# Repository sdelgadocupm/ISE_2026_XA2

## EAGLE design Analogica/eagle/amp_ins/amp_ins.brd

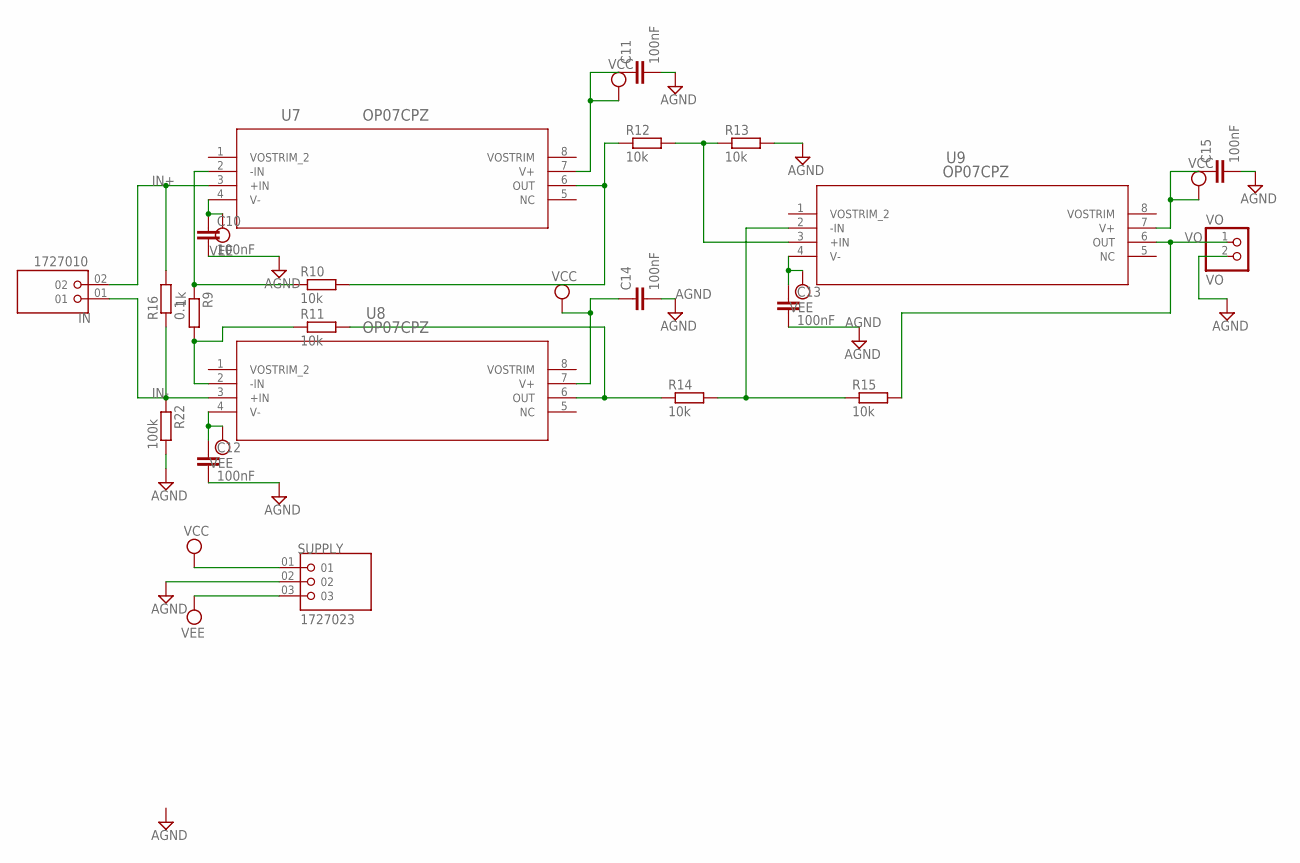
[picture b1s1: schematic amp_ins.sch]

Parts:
C10, C11, C12, C13, C14, C15: 100nF; C075-042X103
IN: 1727010; PHOENIX_1727010
R9: 1k; 0207/10
R10, R11, R12, R13, R14, R15: 10k; 0207/10
R16: 0.1; 0617/17
R22: 100k; 0207/10
SUPPLY: 1727023; PHOENIX_1727023
U7, U8, U9: OP07CPZ; N_8_ADI
VO: VO; 1X02

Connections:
AGND: C10.2, C11.2, C12.2, C13.2, C14.2, C15.2, R13.2, R22.2, SUPPLY.02, VO.2
IN+: IN.02, R16.2, U7.3 (+IN)
IN-: IN.01, R16.1, R22.1, U8.3 (+IN)
unnamed: R9.1, R10.1, U7.2 (-IN)
unnamed: R9.2, R11.1, U8.2 (-IN)
unnamed: R11.2, R14.1, U8.6 (OUT)
unnamed: R10.2, R12.1, U7.6 (OUT)
unnamed: R12.2, R13.1, U9.3 (+IN)
unnamed: R14.2, R15.1, U9.2 (-IN)
VCC: C11.1, C14.1, C15.1, SUPPLY.01, U7.7 (V+), U8.7 (V+), U9.7 (V+)
VEE: C10.1, C12.1, C13.1, SUPPLY.03, U7.4 (V-), U8.4 (V-), U9.4 (V-)
VO: R15.2, U9.6 (OUT), VO.1

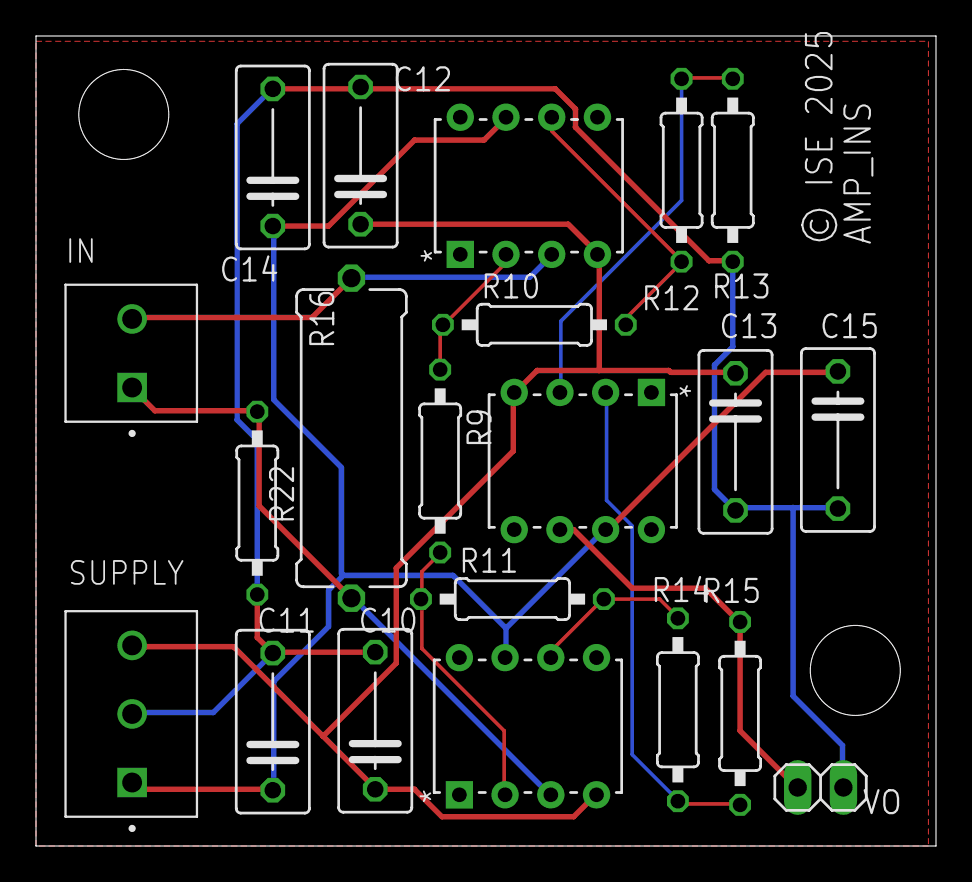
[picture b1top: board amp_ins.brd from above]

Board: 2 copper layers, 50.0 x 45.0 mm, 21 parts (0 on the bottom side), 12 nets.

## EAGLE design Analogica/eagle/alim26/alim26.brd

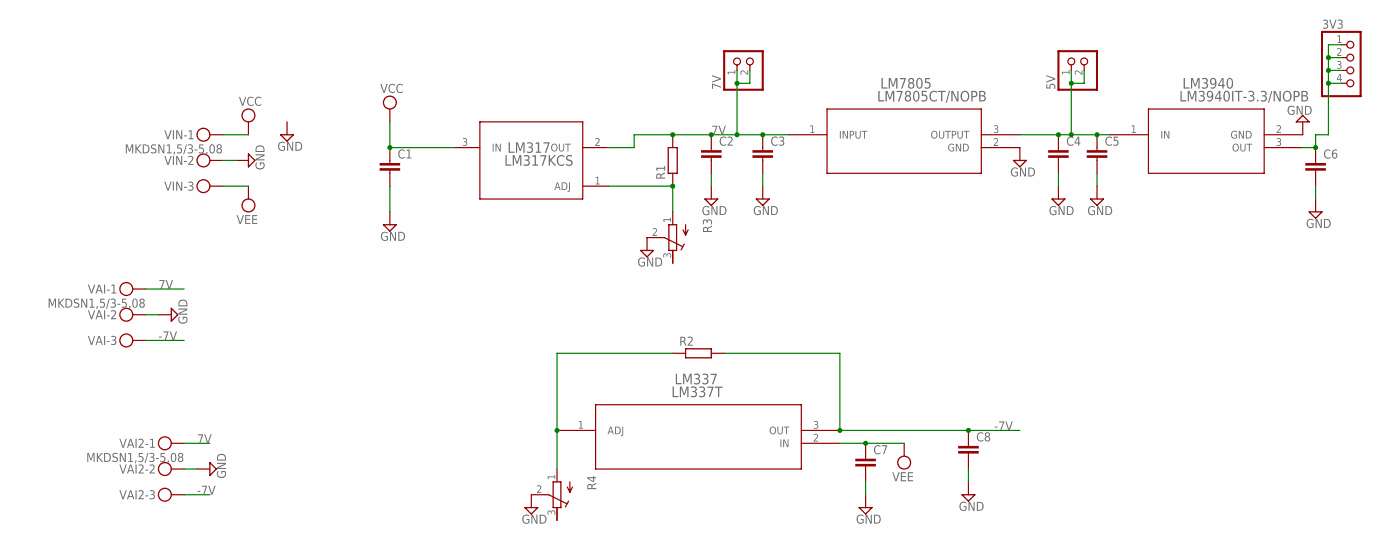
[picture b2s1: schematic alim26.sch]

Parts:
3V3: PINHD-1X4; 1X04
5V, 7V: PINHD-1X2; 1X02
C1, C2, C3, C4, C5, C6, C7, C8: C5/3; C5B3
LM317: LM317KCS; KCS0003A
LM337: LM337T; T03B_TEX
LM3940: LM3940IT-3.3/NOPB; T03B
LM7805: LM7805CT/NOPB; NDE3_TEX
R1, R2: R-EU_0207/10; 0207/10
R3, R4: R-TRIMM64Y; RTRIM64Y
VAI, VAI2: MKDSN1,5/3-5,08
VIN: MKDSN1,5/3-5,08

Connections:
7V: 7V.1, 7V.2, C2.1, C3.1, LM317.2 (OUT), LM7805.1 (INPUT), R1.2, VAI.1, VAI2.1
-7V: C8.1, LM337.3 (OUT), R2.2, VAI.3, VAI2.3
GND: C1.2, C2.2, C3.2, C4.2, C5.2, C6.2, C7.2, C8.2, LM3940.2 (GND), LM7805.2 (GND), R3.2 (S), R4.2 (S), VAI.2, VAI2.2, VIN.2
unnamed: LM317.1 (ADJ), R1.1, R3.1 (A)
unnamed: 5V.1, 5V.2, C4.1, C5.1, LM3940.1 (IN), LM7805.3 (OUTPUT)
unnamed: 3V3.1, 3V3.2, 3V3.3, 3V3.4, C6.1, LM3940.3 (OUT)
unnamed: LM337.1 (ADJ), R2.1, R4.1 (A)
VCC: C1.1, LM317.3 (IN), VIN.1
VEE: C7.1, LM337.2 (IN), VIN.3

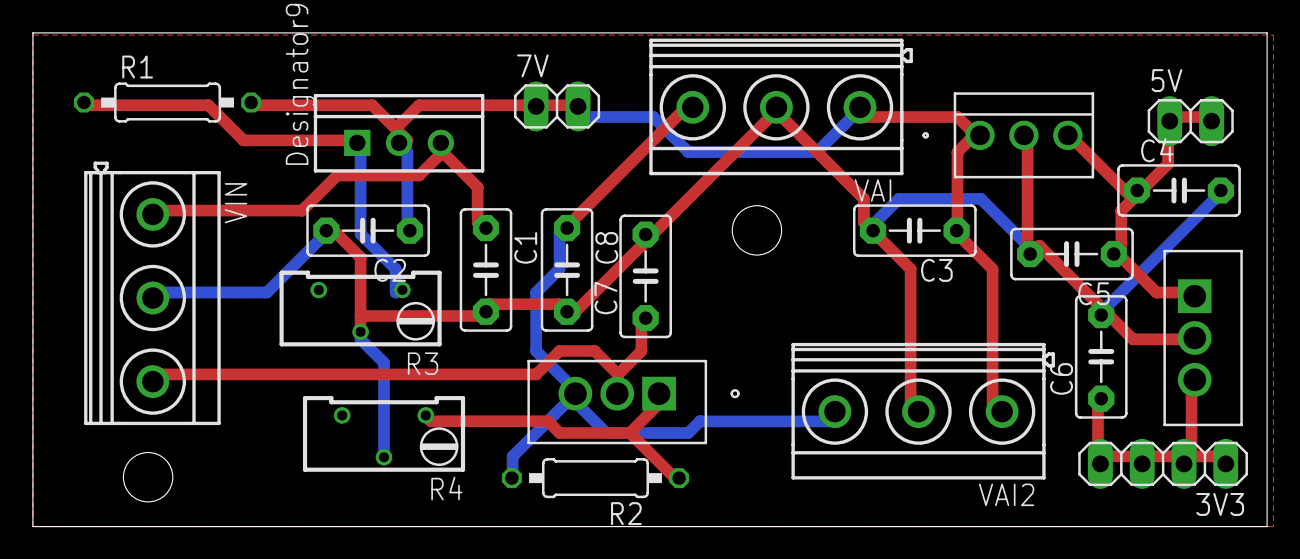
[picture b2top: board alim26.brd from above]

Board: 2 copper layers, 75.0 x 30.0 mm, 22 parts (0 on the bottom side), 9 nets.

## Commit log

2026-04-18 Placa Autonoma casi completa
2026-04-22 ajustes placa autónoma e idea de UART
2026-04-24 Placa autónoma funcionando completamente comentada
2026-04-24 Interfaz Web
2026-04-27 Primer commit de la placa master,USART y demas
2026-04-28 alimentacion y A.instrumentacion
2026-04-28 UART TX y RX
2026-04-29 Conexión entre placas comprobada
2026-04-29 Se me habia olvidado subir la slave
2026-04-30 UART para probar
2026-05-02 Comunicaciones terminadas junto con logger memoria
2026-05-02 cgi completo
2026-05-02 Master.c completo
2026-05-03 Codigo terminado, versiones casi finales de Autonoma y Master
2026-05-04 Filtro adc
2026-05-09 Perfeccionamiento Servidor + comentarios
2026-05-13 Código Final

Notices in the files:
Analogica/eagle/alim26/alim26.brd:
© ISE_2026
Analogica/eagle/amp_ins/amp_ins.brd:
© ISE 2025
parts and their libraries:
COPYRIGHT: Copyright (C) 2026 Ultra Librarian. All rights reserved.
COPYRIGHT: Copyright (C) 2025 Ultra Librarian. All rights reserved.
COPYRIGHT: Copyright (C) 2024 Ultra Librarian. All rights reserved.
